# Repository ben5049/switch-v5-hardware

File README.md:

# Switch v5 Hardware (WIP)

KiCad design files for the 5th iteration of my single pair Ethernet (SPE) switch. It is similar to [v4](https://github.com/ben5049/switch-v4-hardware) but with more ports and an RJ45 connector so an external media converter isn't needed to connect to regular Ethernet networks.

## Versions

| Version | Description |
| ------- | ----------- |
| v5.1.0  | Fixed bugs from first revision |
| v5.0.0  | First release |

See the [errata](docs/errata.md) for details on bugs.

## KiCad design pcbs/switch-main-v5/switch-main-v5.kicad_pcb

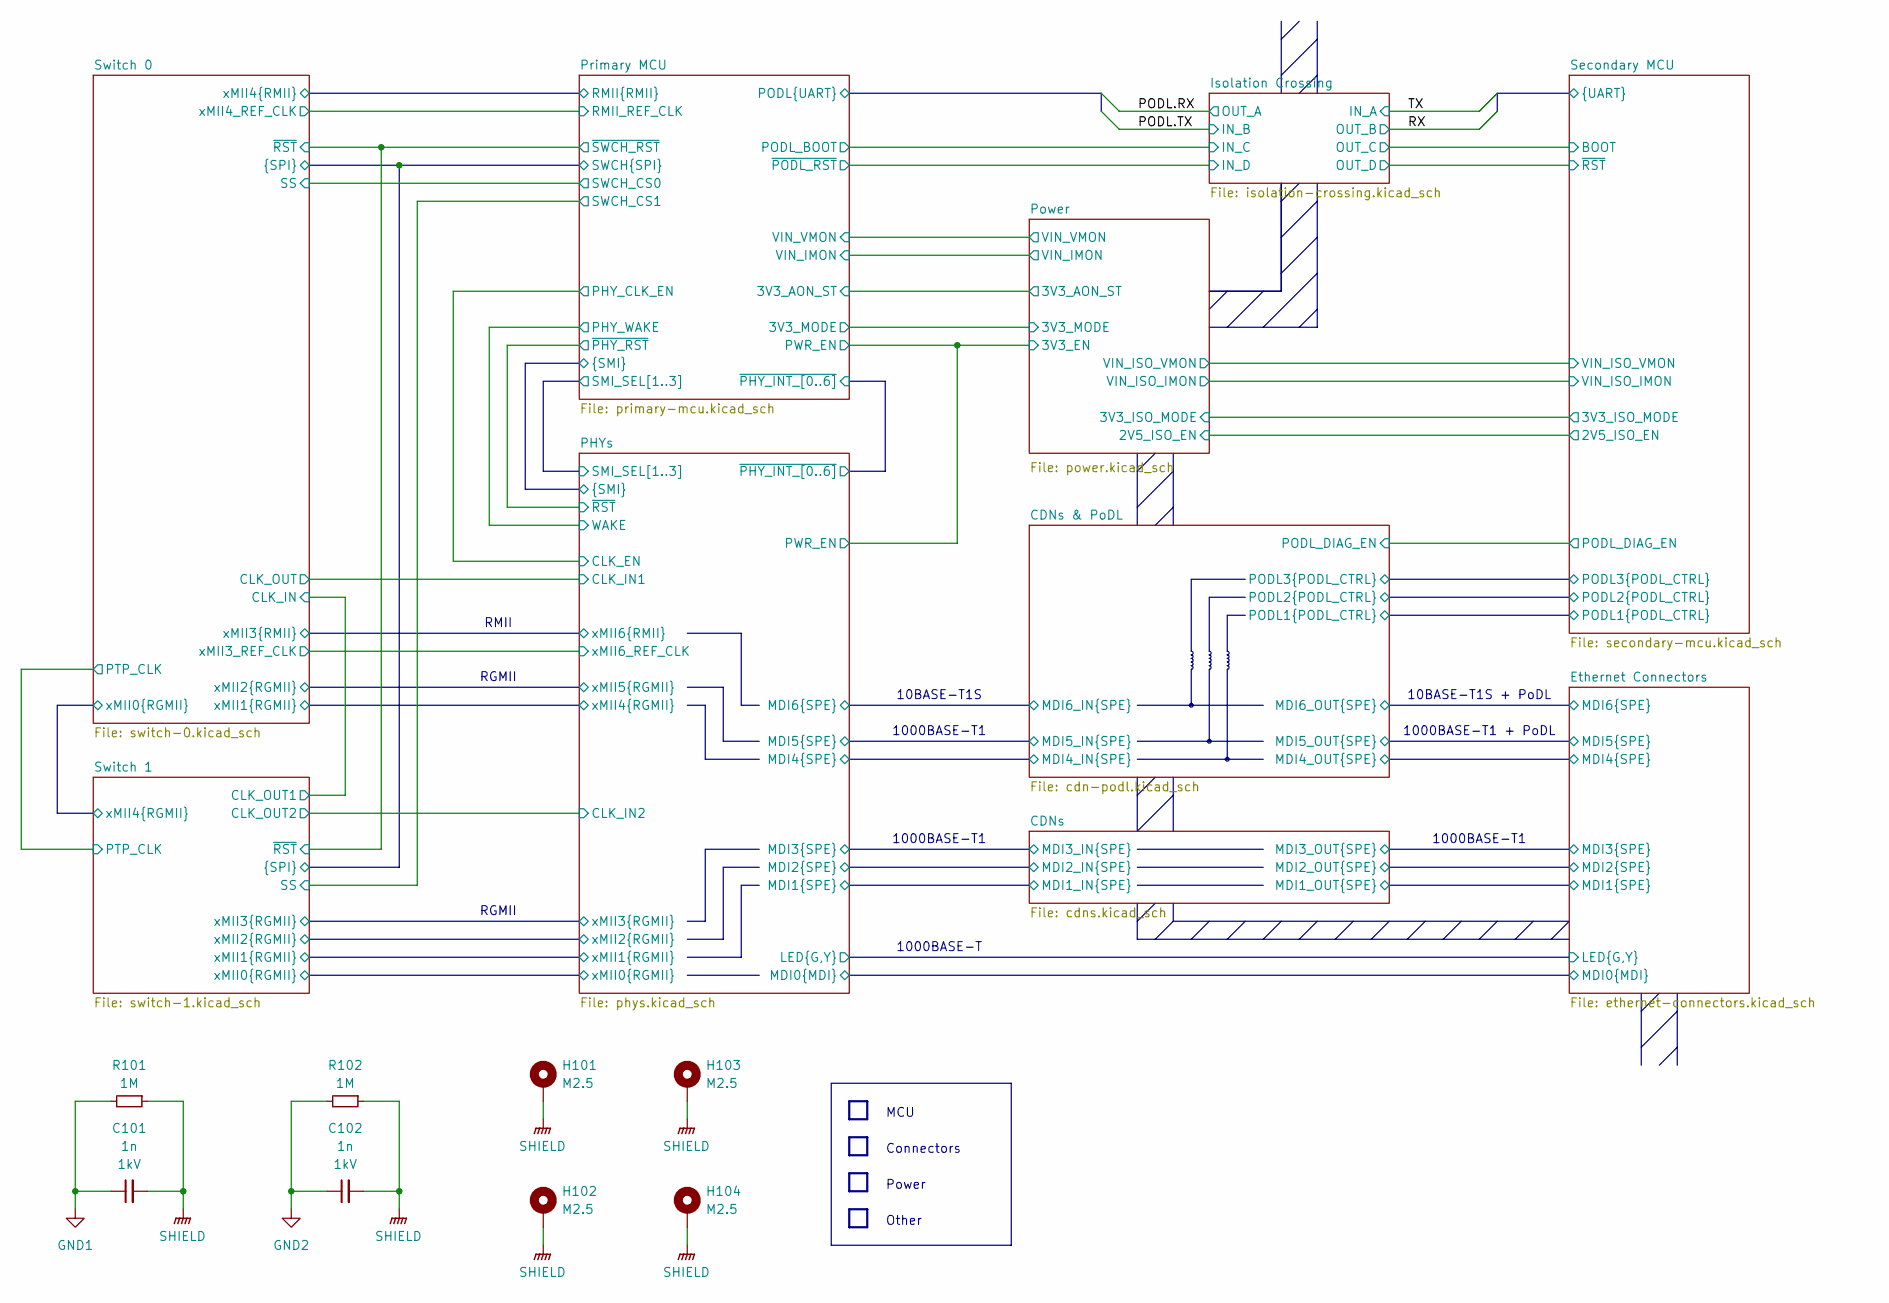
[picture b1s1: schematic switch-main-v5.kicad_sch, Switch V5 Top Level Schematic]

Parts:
C101, C102: 1n; C_0805; Voltage 1kV
H101, H102, H103, H104: M2.5; MountingHole_2.7mm_M2.5_Pad
R101, R102: 1M; R_0805

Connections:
GND1: C101.1, R101.2; also elsewhere on the board
GND2: C102.1, R102.2; also elsewhere on the board
SHIELD: C101.2, C102.2, H101.1 (1_1), H102.1 (1_1), H103.1 (1_1), H104.1 (1_1), R101.1, R102.1; also elsewhere on the board

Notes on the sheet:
10BASE-T1S
1000BASE-T1
Power
RGMII
Other
1000BASE-T
RMII
Connectors
1000BASE-T1 + PoDL
MCU
10BASE-T1S + PoDL

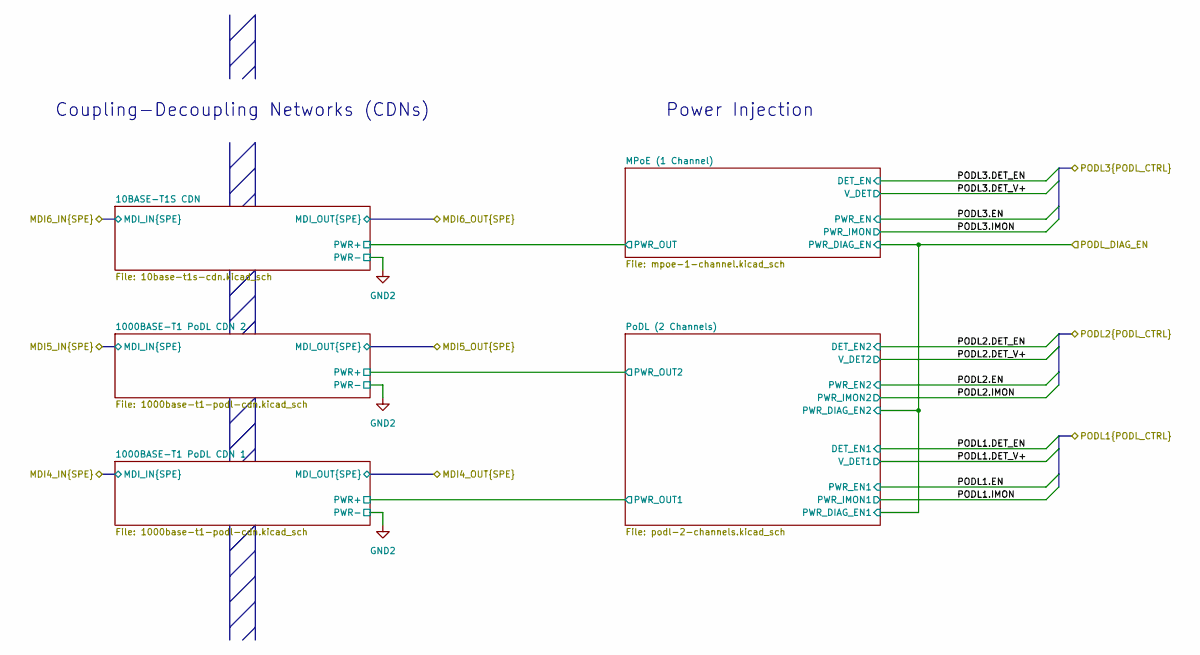
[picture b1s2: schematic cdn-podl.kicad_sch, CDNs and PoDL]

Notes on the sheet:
Power Injection
Coupling-Decoupling Networks (CDNs)

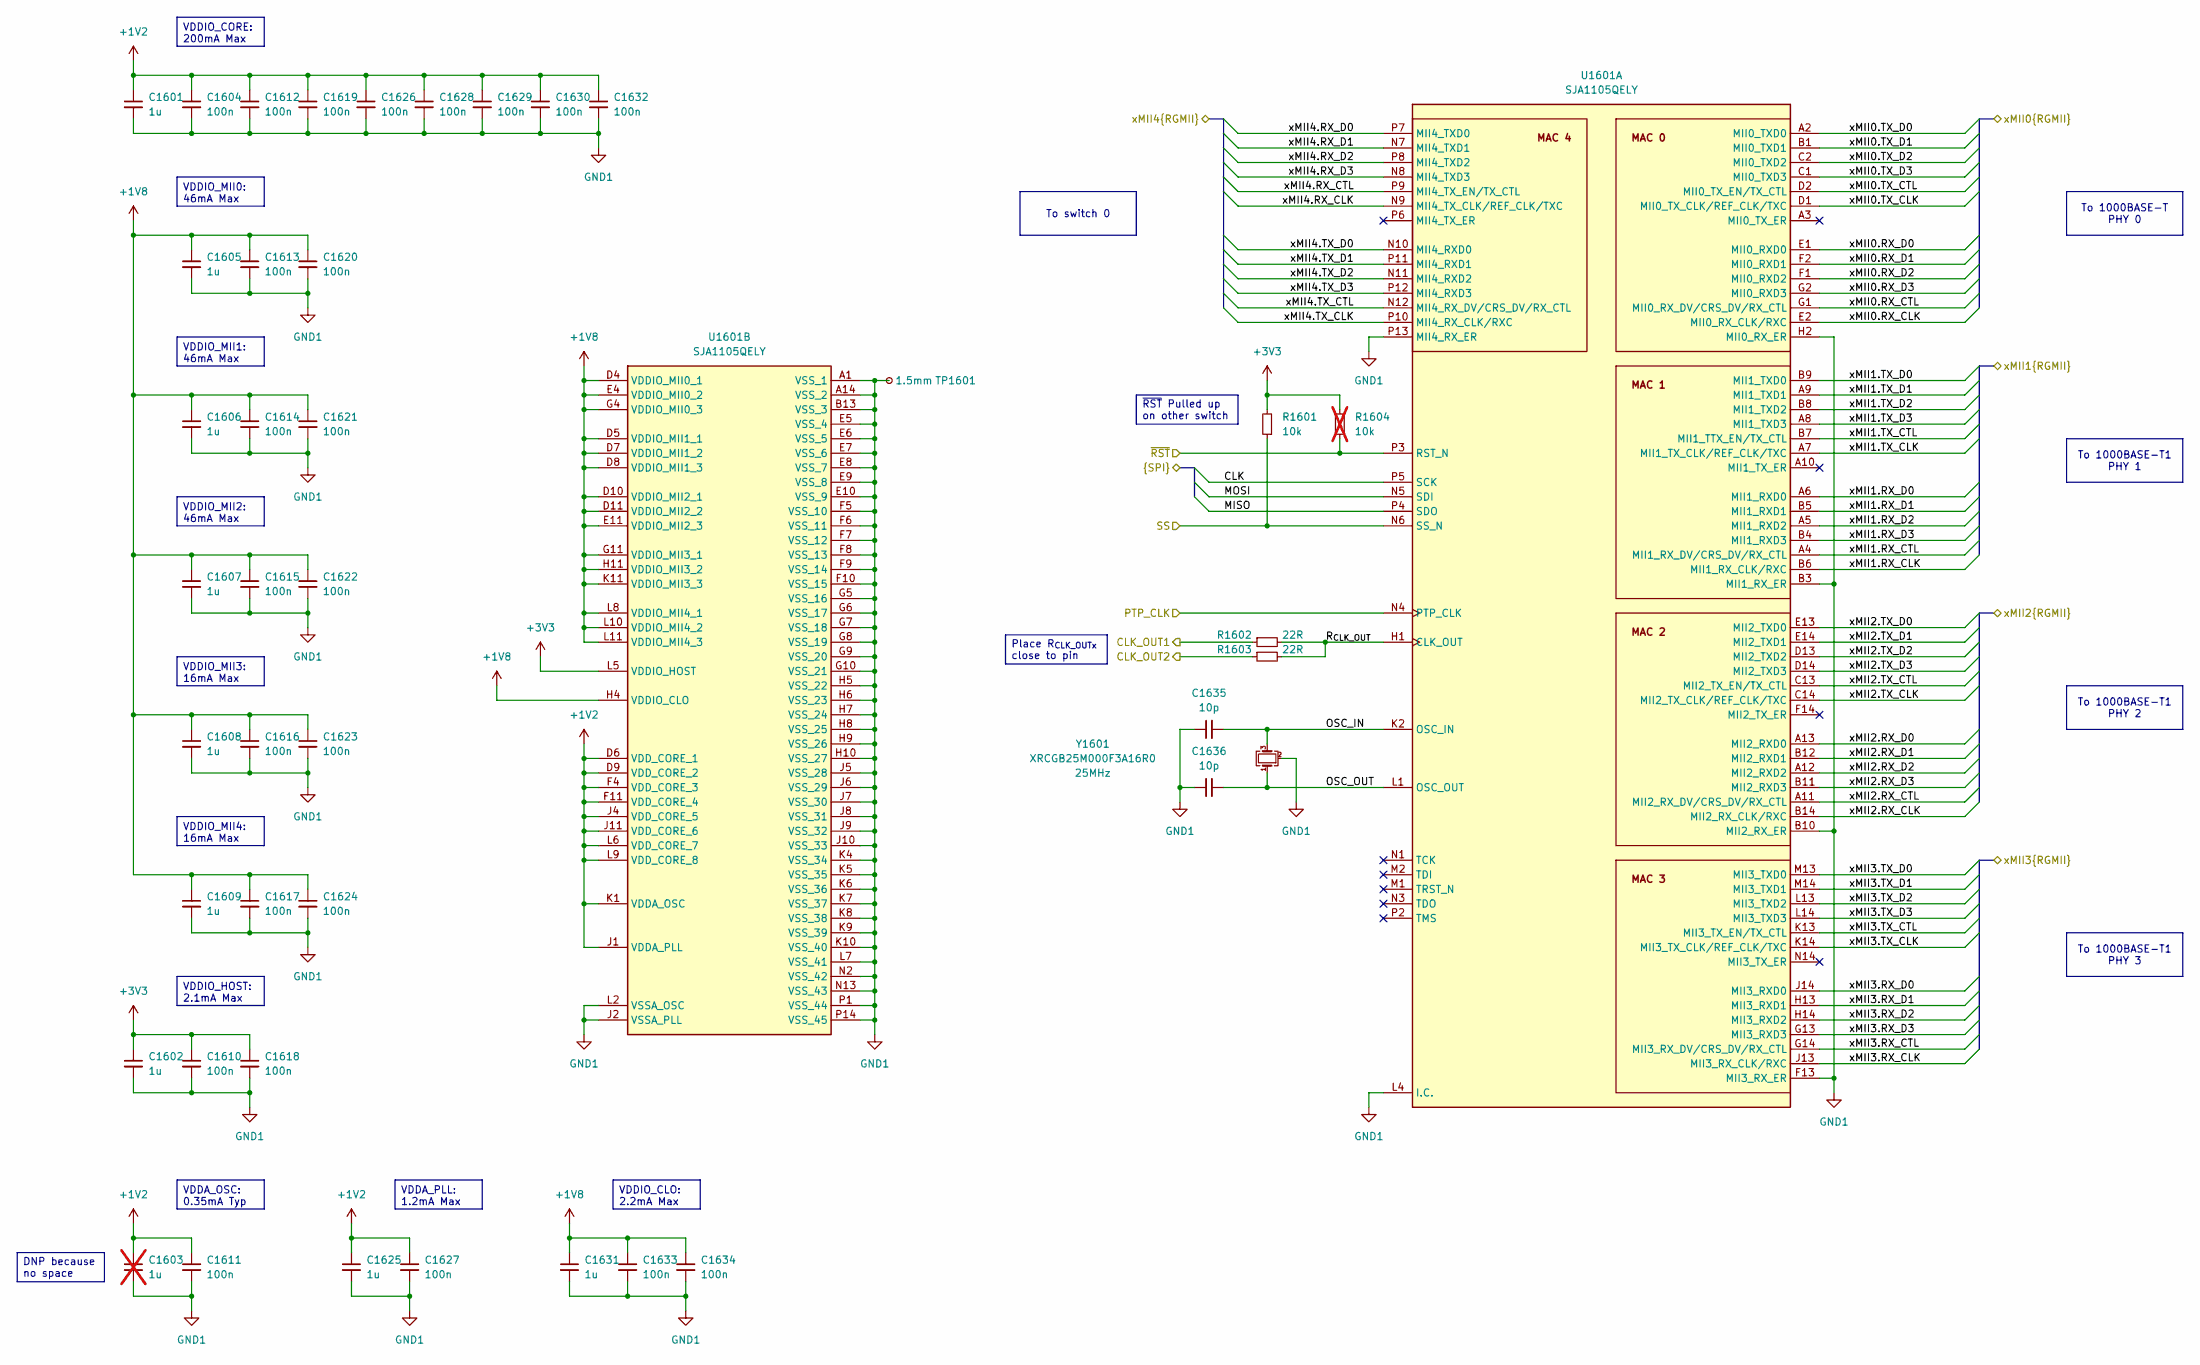
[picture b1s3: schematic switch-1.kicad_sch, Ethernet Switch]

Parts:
C1601, C1602, C1605, C1606, C1607, C1608, C1609, C1625, C1631: 1u; C_0402
C1603: 1u; C_0402_1005Metric; not fitted
C1604, C1610, C1611, C1612, C1613, C1614, C1615, C1616, C1617, C1618, C1619, C1620, C1621, C1622, C1623, C1624, C1626, C1627, C1628, C1629, C1630, C1632, C1633, C1634: 100n; C_0402
C1635, C1636: 10p; C_0402
R1601: 10k; R_0402
R1602, R1603: 22R; R_0402
R1604: 10k; R_0402_1005Metric; not fitted
TP1601: 1.5mm; TestPoint_Pad_D1.5mm
U1601: SJA1105QELY; BGA159C80P14X14_1200X1200X150; Mouser Part Number 771-SJA1105QELY
Y1601: XRCGB25M000F3A16R0

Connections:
+1V2: C1601.1, C1603.1, C1604.1, C1611.1, C1612.1, C1619.1, C1625.1, C1626.1, C1627.1, C1628.1, C1629.1, C1630.1, C1632.1, U1601.D6 (VDD_CORE_1), U1601.D9 (VDD_CORE_2), U1601.F4 (VDD_CORE_3), U1601.F11 (VDD_CORE_4), U1601.J1 (VDDA_PLL), U1601.J4 (VDD_CORE_5), U1601.J11 (VDD_CORE_6), U1601.K1 (VDDA_OSC), U1601.L6 (VDD_CORE_7), U1601.L9 (VDD_CORE_8); also elsewhere on the board
+1V8: C1605.1, C1606.1, C1607.1, C1608.1, C1609.1, C1613.1, C1614.1, C1615.1, C1616.1, C1617.1, C1620.1, C1621.1, C1622.1, C1623.1, C1624.1, C1631.1, C1633.1, C1634.1, U1601.D4 (VDDIO_MII0_1), U1601.D5 (VDDIO_MII1_1), U1601.D7 (VDDIO_MII1_2), U1601.D8 (VDDIO_MII1_3), U1601.D10 (VDDIO_MII2_1), U1601.D11 (VDDIO_MII2_2), U1601.E4 (VDDIO_MII0_2), U1601.E11 (VDDIO_MII2_3), U1601.G4 (VDDIO_MII0_3), U1601.G11 (VDDIO_MII3_1), U1601.H4 (VDDIO_CLO), U1601.H11 (VDDIO_MII3_2), U1601.K11 (VDDIO_MII3_3), U1601.L8 (VDDIO_MII4_1), U1601.L10 (VDDIO_MII4_2), U1601.L11 (VDDIO_MII4_3); also elsewhere on the board
+3V3: C1602.1, C1610.1, C1618.1, R1601.2, R1604.2, U1601.L5 (VDDIO_HOST); also elsewhere on the board
/PHYs/CLK_IN2: R1603.1; also elsewhere on the board
/PHYs/xMII0.RX_CLK: U1601.E2 (MII0_RX_CLK/RXC); also elsewhere on the board
/PHYs/xMII0.RX_CTL: U1601.G1 (MII0_RX_DV/CRS_DV/RX_CTL); also elsewhere on the board
/PHYs/xMII0.RX_D0: U1601.E1 (MII0_RXD0); also elsewhere on the board
/PHYs/xMII0.RX_D1: U1601.F2 (MII0_RXD1); also elsewhere on the board
/PHYs/xMII0.RX_D2: U1601.F1 (MII0_RXD2); also elsewhere on the board
/PHYs/xMII0.RX_D3: U1601.G2 (MII0_RXD3); also elsewhere on the board
/PHYs/xMII0.TX_CLK: U1601.D1 (MII0_TX_CLK/REF_CLK/TXC); also elsewhere on the board
/PHYs/xMII0.TX_CTL: U1601.D2 (MII0_TX_EN/TX_CTL); also elsewhere on the board
/PHYs/xMII0.TX_D0: U1601.A2 (MII0_TXD0); also elsewhere on the board
/PHYs/xMII0.TX_D1: U1601.B1 (MII0_TXD1); also elsewhere on the board
/PHYs/xMII0.TX_D2: U1601.C2 (MII0_TXD2); also elsewhere on the board
/PHYs/xMII0.TX_D3: U1601.C1 (MII0_TXD3); also elsewhere on the board
/PHYs/xMII1.RX_CLK: U1601.B6 (MII1_RX_CLK/RXC); also elsewhere on the board
/PHYs/xMII1.RX_CTL: U1601.A4 (MII1_RX_DV/CRS_DV/RX_CTL); also elsewhere on the board
/PHYs/xMII1.RX_D0: U1601.A6 (MII1_RXD0); also elsewhere on the board
/PHYs/xMII1.RX_D1: U1601.B5 (MII1_RXD1); also elsewhere on the board
/PHYs/xMII1.RX_D2: U1601.A5 (MII1_RXD2); also elsewhere on the board
/PHYs/xMII1.RX_D3: U1601.B4 (MII1_RXD3); also elsewhere on the board
/PHYs/xMII1.TX_CLK: U1601.A7 (MII1_TX_CLK/REF_CLK/TXC); also elsewhere on the board
/PHYs/xMII1.TX_CTL: U1601.B7 (MII1_TTX_EN/TX_CTL); also elsewhere on the board
/PHYs/xMII1.TX_D0: U1601.B9 (MII1_TXD0); also elsewhere on the board
/PHYs/xMII1.TX_D1: U1601.A9 (MII1_TXD1); also elsewhere on the board
/PHYs/xMII1.TX_D2: U1601.B8 (MII1_TXD2); also elsewhere on the board
/PHYs/xMII1.TX_D3: U1601.A8 (MII1_TXD3); also elsewhere on the board
/PHYs/xMII2.RX_CLK: U1601.B14 (MII2_RX_CLK/RXC); also elsewhere on the board
/PHYs/xMII2.RX_CTL: U1601.A11 (MII2_RX_DV/CRS_DV/RX_CTL); also elsewhere on the board
/PHYs/xMII2.RX_D0: U1601.A13 (MII2_RXD0); also elsewhere on the board
/PHYs/xMII2.RX_D1: U1601.B12 (MII2_RXD1); also elsewhere on the board
/PHYs/xMII2.RX_D2: U1601.A12 (MII2_RXD2); also elsewhere on the board
/PHYs/xMII2.RX_D3: U1601.B11 (MII2_RXD3); also elsewhere on the board
/PHYs/xMII2.TX_CLK: U1601.C14 (MII2_TX_CLK/REF_CLK/TXC); also elsewhere on the board
/PHYs/xMII2.TX_CTL: U1601.C13 (MII2_TX_EN/TX_CTL); also elsewhere on the board
/PHYs/xMII2.TX_D0: U1601.E13 (MII2_TXD0); also elsewhere on the board
/PHYs/xMII2.TX_D1: U1601.E14 (MII2_TXD1); also elsewhere on the board
/PHYs/xMII2.TX_D2: U1601.D13 (MII2_TXD2); also elsewhere on the board
/PHYs/xMII2.TX_D3: U1601.D14 (MII2_TXD3); also elsewhere on the board
/PHYs/xMII3.RX_CLK: U1601.J13 (MII3_RX_CLK/RXC); also elsewhere on the board
/PHYs/xMII3.RX_CTL: U1601.G14 (MII3_RX_DV/CRS_DV/RX_CTL); also elsewhere on the board
/PHYs/xMII3.RX_D0: U1601.J14 (MII3_RXD0); also elsewhere on the board
/PHYs/xMII3.RX_D1: U1601.H13 (MII3_RXD1); also elsewhere on the board
/PHYs/xMII3.RX_D2: U1601.H14 (MII3_RXD2); also elsewhere on the board
/PHYs/xMII3.RX_D3: U1601.G13 (MII3_RXD3); also elsewhere on the board
/PHYs/xMII3.TX_CLK: U1601.K14 (MII3_TX_CLK/REF_CLK/TXC); also elsewhere on the board
/PHYs/xMII3.TX_CTL: U1601.K13 (MII3_TX_EN/TX_CTL); also elsewhere on the board
/PHYs/xMII3.TX_D0: U1601.M13 (MII3_TXD0); also elsewhere on the board
/PHYs/xMII3.TX_D1: U1601.M14 (MII3_TXD1); also elsewhere on the board
/PHYs/xMII3.TX_D2: U1601.L13 (MII3_TXD2); also elsewhere on the board
/PHYs/xMII3.TX_D3: U1601.L14 (MII3_TXD3); also elsewhere on the board
/Primary MCU/SWCH.CLK: U1601.P5 (SCK); also elsewhere on the board
/Primary MCU/SWCH.MISO: U1601.P4 (SDO); also elsewhere on the board
/Primary MCU/SWCH.MOSI: U1601.N5 (SDI); also elsewhere on the board
/Primary MCU/SWCH_CS1: R1601.1, U1601.N6 (SS_N); also elsewhere on the board
/Primary MCU/~SWCH_RST: R1604.1, U1601.P3 (RST_N); also elsewhere on the board
/Switch 0/CLK_IN: R1602.1; also elsewhere on the board
/Switch 0/PTP_CLK: U1601.N4 (PTP_CLK); also elsewhere on the board
/Switch 0/xMII0.RX_CLK: U1601.N9 (MII4_TX_CLK/REF_CLK/TXC); also elsewhere on the board
/Switch 0/xMII0.RX_CTL: U1601.P9 (MII4_TX_EN/TX_CTL); also elsewhere on the board
/Switch 0/xMII0.RX_D0: U1601.P7 (MII4_TXD0); also elsewhere on the board
/Switch 0/xMII0.RX_D1: U1601.N7 (MII4_TXD1); also elsewhere on the board
/Switch 0/xMII0.RX_D2: U1601.P8 (MII4_TXD2); also elsewhere on the board
/Switch 0/xMII0.RX_D3: U1601.N8 (MII4_TXD3); also elsewhere on the board
/Switch 0/xMII0.TX_CLK: U1601.P10 (MII4_RX_CLK/RXC); also elsewhere on the board
/Switch 0/xMII0.TX_CTL: U1601.N12 (MII4_RX_DV/CRS_DV/RX_CTL); also elsewhere on the board
/Switch 0/xMII0.TX_D0: U1601.N10 (MII4_RXD0); also elsewhere on the board
/Switch 0/xMII0.TX_D1: U1601.P11 (MII4_RXD1); also elsewhere on the board
/Switch 0/xMII0.TX_D2: U1601.N11 (MII4_RXD2); also elsewhere on the board
/Switch 0/xMII0.TX_D3: U1601.P12 (MII4_RXD3); also elsewhere on the board
/Switch 1/OSC_IN: C1635.2, U1601.K2 (OSC_IN), Y1601.3
/Switch 1/OSC_OUT: C1636.2, U1601.L1 (OSC_OUT), Y1601.1
/Switch 1/R_{CLK_OUT}: R1602.2, R1603.2, U1601.H1 (CLK_OUT)
GND1: C1601.2, C1602.2, C1603.2, C1604.2, C1605.2, C1606.2, C1607.2, C1608.2, C1609.2, C1610.2, C1611.2, C1612.2, C1613.2, C1614.2, C1615.2, C1616.2, C1617.2, C1618.2, C1619.2, C1620.2, C1621.2, C1622.2, C1623.2, C1624.2, C1625.2, C1626.2, C1627.2, C1628.2, C1629.2, C1630.2, C1631.2, C1632.2, C1633.2, C1634.2, C1635.1, C1636.1, TP1601.1 (1_1), U1601.A1 (VSS_1), U1601.A14 (VSS_2), U1601.B3 (MII1_RX_ER), U1601.B10 (MII2_RX_ER), U1601.B13 (VSS_3), U1601.E5 (VSS_4), U1601.E6 (VSS_5), U1601.E7 (VSS_6), U1601.E8 (VSS_7), U1601.E9 (VSS_8), U1601.E10 (VSS_9), U1601.F5 (VSS_10), U1601.F6 (VSS_11), U1601.F7 (VSS_12), U1601.F8 (VSS_13), U1601.F9 (VSS_14), U1601.F10 (VSS_15), U1601.F13 (MII3_RX_ER), U1601.G5 (VSS_16), U1601.G6 (VSS_17), U1601.G7 (VSS_18), U1601.G8 (VSS_19), U1601.G9 (VSS_20), U1601.G10 (VSS_21), U1601.H2 (MII0_RX_ER), U1601.H5 (VSS_22), U1601.H6 (VSS_23), U1601.H7 (VSS_24), U1601.H8 (VSS_25), U1601.H9 (VSS_26), U1601.H10 (VSS_27), U1601.J2 (VSSA_PLL), U1601.J5 (VSS_28), U1601.J6 (VSS_29), U1601.J7 (VSS_30), U1601.J8 (VSS_31), U1601.J9 (VSS_32), U1601.J10 (VSS_33), U1601.K4 (VSS_34), U1601.K5 (VSS_35), U1601.K6 (VSS_36), U1601.K7 (VSS_37), U1601.K8 (VSS_38), U1601.K9 (VSS_39), U1601.K10 (VSS_40), U1601.L2 (VSSA_OSC), U1601.L4 (I.C.), U1601.L7 (VSS_41), U1601.N2 (VSS_42), U1601.N13 (VSS_43), U1601.P1 (VSS_44), U1601.P13 (MII4_RX_ER), U1601.P14 (VSS_45), Y1601.2 (G), Y1601.4 (G); also elsewhere on the board

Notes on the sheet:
To 1000BASE-T1 PHY 1
To 1000BASE-T1 PHY 2
VDDIO_MII3: 16mA Max
~{RST} Pulled up on other switch
To 1000BASE-T1 PHY 3
VDDIO_CLO: 2.2mA Max
VDDIO_MII2: 46mA Max
VDDIO_HOST: 2.1mA Max
VDDA_OSC: 0.35mA Typ
DNP because no space
VDDIO_MII0: 46mA Max
To switch 0
VDDA_PLL: 1.2mA Max
VDDIO_CORE: 200mA Max
Place R_{CLK_OUTx} close to pin
To 1000BASE-T PHY 0
VDDIO_MII4: 16mA Max
VDDIO_MII1: 46mA Max

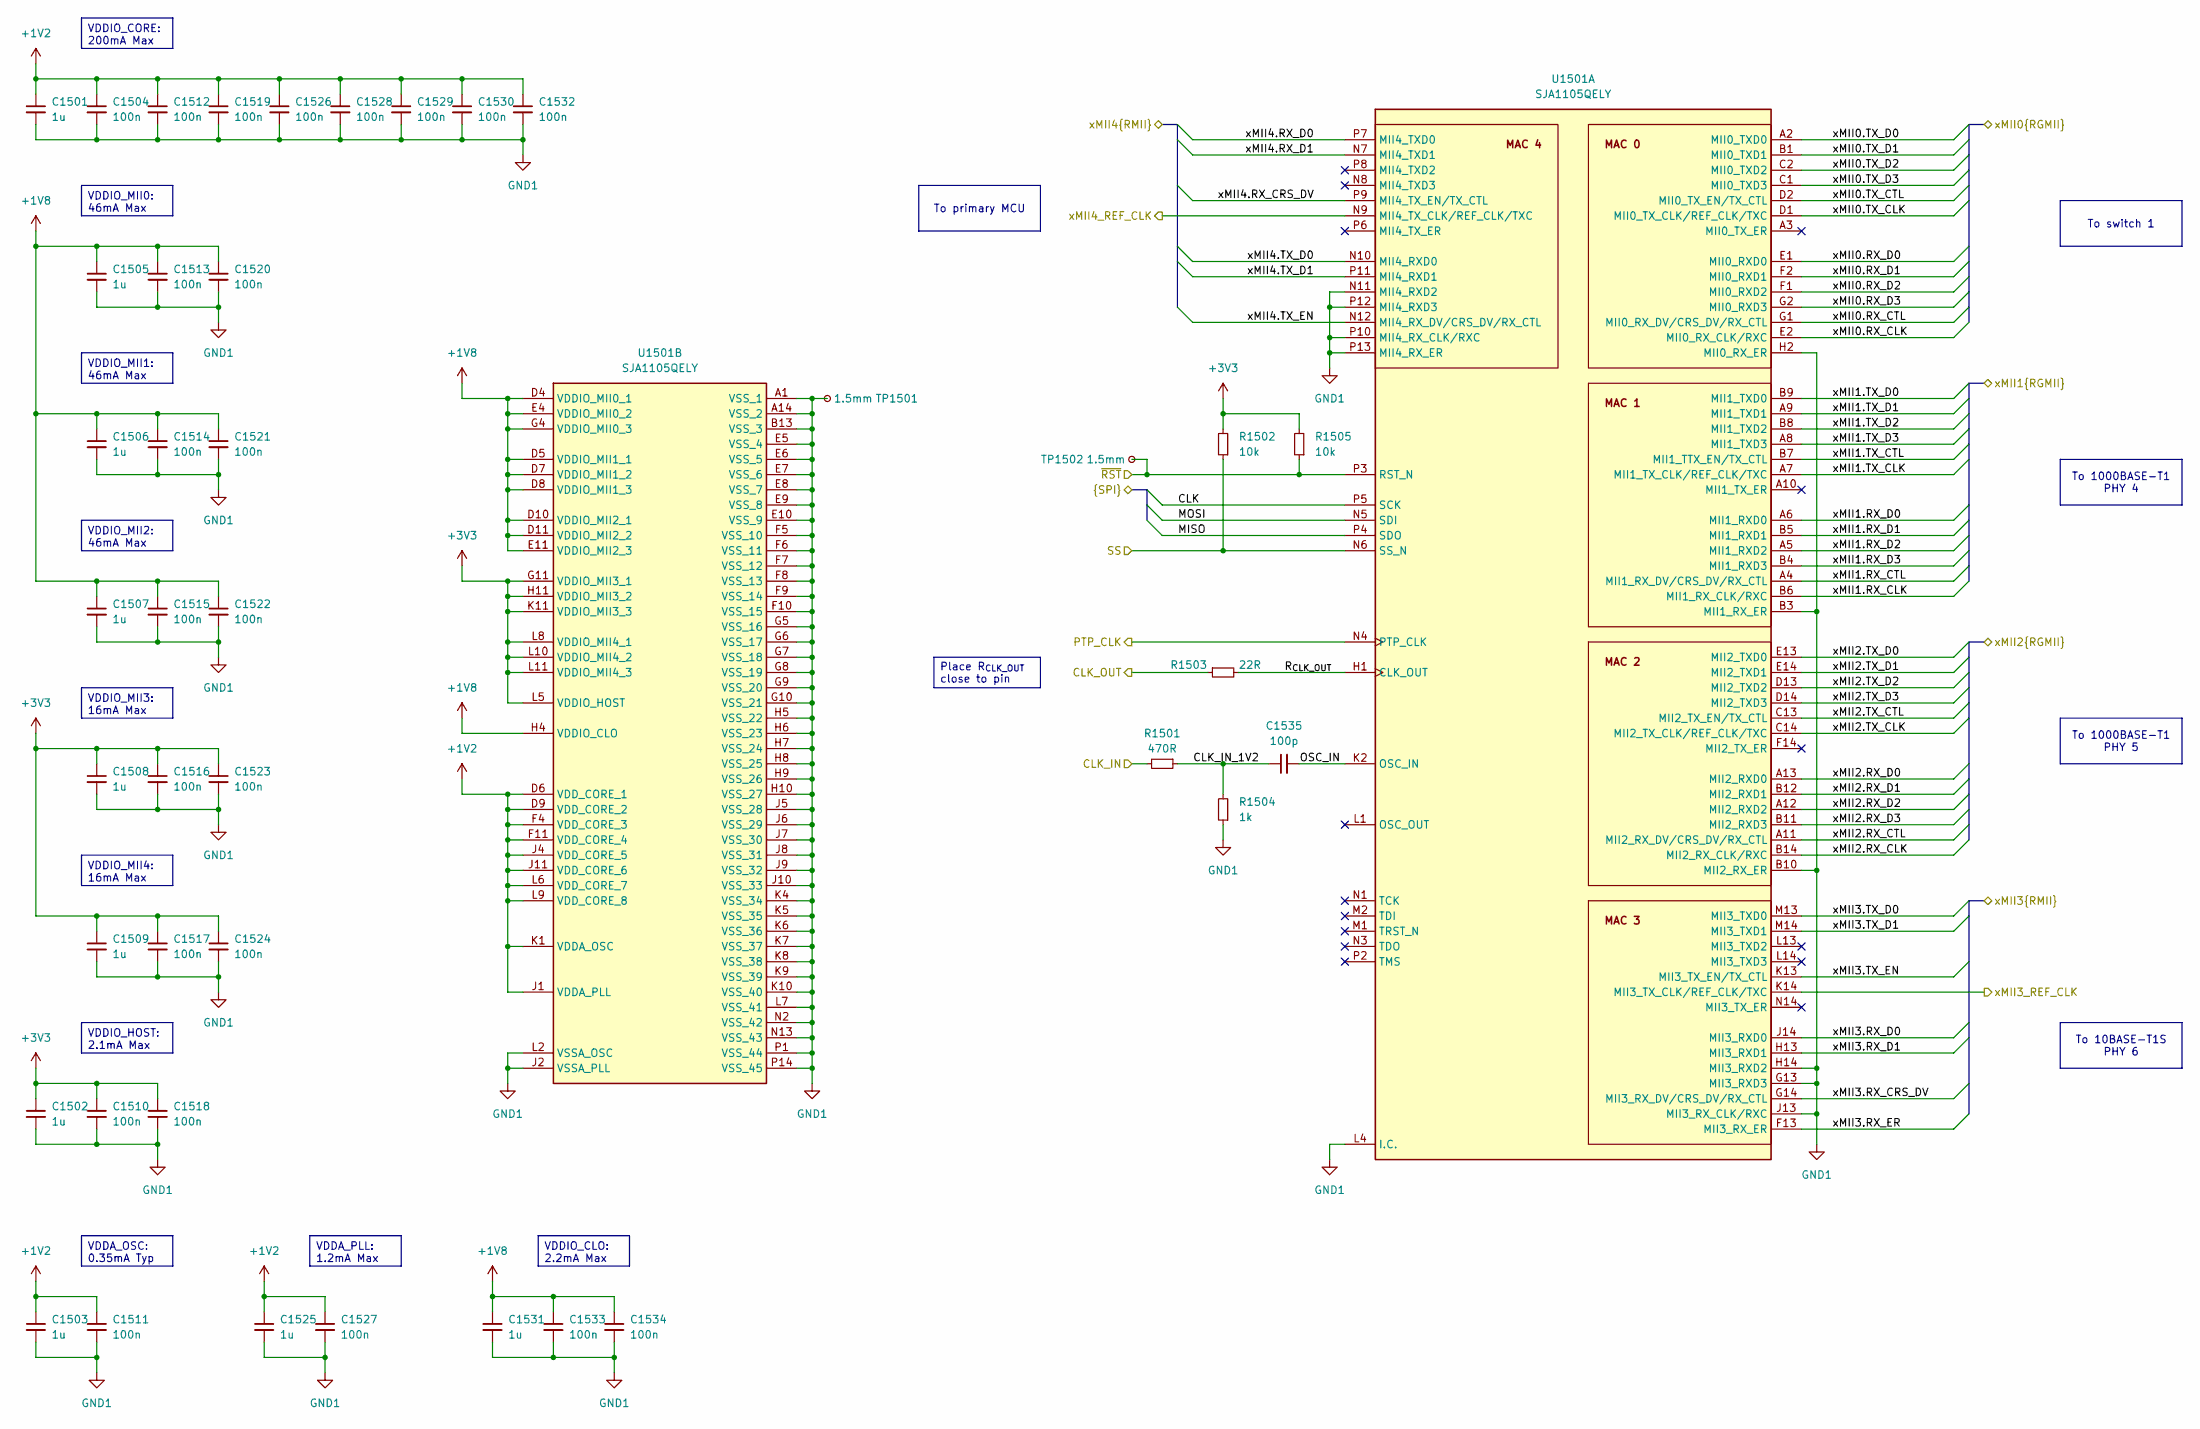
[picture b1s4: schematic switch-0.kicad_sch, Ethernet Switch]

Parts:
C1501, C1502, C1503, C1505, C1506, C1507, C1508, C1509, C1525, C1531: 1u; C_0402
C1504, C1510, C1511, C1512, C1513, C1514, C1515, C1516, C1517, C1518, C1519, C1520, C1521, C1522, C1523, C1524, C1526, C1527, C1528, C1529, C1530, C1532, C1533, C1534: 100n; C_0402
C1535: 100p; C_0402
R1501: 470R; R_0402
R1502, R1505: 10k; R_0402
R1503: 22R; R_0402
R1504: 1k; R_0402
TP1501, TP1502: 1.5mm; TestPoint_Pad_D1.5mm
U1501: SJA1105QELY; BGA159C80P14X14_1200X1200X150; Mouser Part Number 771-SJA1105QELY

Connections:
+1V2: C1501.1, C1503.1, C1504.1, C1511.1, C1512.1, C1519.1, C1525.1, C1526.1, C1527.1, C1528.1, C1529.1, C1530.1, C1532.1, U1501.D6 (VDD_CORE_1), U1501.D9 (VDD_CORE_2), U1501.F4 (VDD_CORE_3), U1501.F11 (VDD_CORE_4), U1501.J1 (VDDA_PLL), U1501.J4 (VDD_CORE_5), U1501.J11 (VDD_CORE_6), U1501.K1 (VDDA_OSC), U1501.L6 (VDD_CORE_7), U1501.L9 (VDD_CORE_8); also elsewhere on the board
+1V8: C1505.1, C1506.1, C1507.1, C1513.1, C1514.1, C1515.1, C1520.1, C1521.1, C1522.1, C1531.1, C1533.1, C1534.1, U1501.D4 (VDDIO_MII0_1), U1501.D5 (VDDIO_MII1_1), U1501.D7 (VDDIO_MII1_2), U1501.D8 (VDDIO_MII1_3), U1501.D10 (VDDIO_MII2_1), U1501.D11 (VDDIO_MII2_2), U1501.E4 (VDDIO_MII0_2), U1501.E11 (VDDIO_MII2_3), U1501.G4 (VDDIO_MII0_3), U1501.H4 (VDDIO_CLO); also elsewhere on the board
+3V3: C1502.1, C1508.1, C1509.1, C1510.1, C1516.1, C1517.1, C1518.1, C1523.1, C1524.1, R1502.2, R1505.2, U1501.G11 (VDDIO_MII3_1), U1501.H11 (VDDIO_MII3_2), U1501.K11 (VDDIO_MII3_3), U1501.L5 (VDDIO_HOST), U1501.L8 (VDDIO_MII4_1), U1501.L10 (VDDIO_MII4_2), U1501.L11 (VDDIO_MII4_3); also elsewhere on the board
/PHYs/CLK_IN1: R1503.1; also elsewhere on the board
/PHYs/xMII4.RX_CLK: U1501.B6 (MII1_RX_CLK/RXC); also elsewhere on the board
/PHYs/xMII4.RX_CTL: U1501.A4 (MII1_RX_DV/CRS_DV/RX_CTL); also elsewhere on the board
/PHYs/xMII4.RX_D0: U1501.A6 (MII1_RXD0); also elsewhere on the board
/PHYs/xMII4.RX_D1: U1501.B5 (MII1_RXD1); also elsewhere on the board
/PHYs/xMII4.RX_D2: U1501.A5 (MII1_RXD2); also elsewhere on the board
/PHYs/xMII4.RX_D3: U1501.B4 (MII1_RXD3); also elsewhere on the board
/PHYs/xMII4.TX_CLK: U1501.A7 (MII1_TX_CLK/REF_CLK/TXC); also elsewhere on the board
/PHYs/xMII4.TX_CTL: U1501.B7 (MII1_TTX_EN/TX_CTL); also elsewhere on the board
/PHYs/xMII4.TX_D0: U1501.B9 (MII1_TXD0); also elsewhere on the board
/PHYs/xMII4.TX_D1: U1501.A9 (MII1_TXD1); also elsewhere on the board
/PHYs/xMII4.TX_D2: U1501.B8 (MII1_TXD2); also elsewhere on the board
/PHYs/xMII4.TX_D3: U1501.A8 (MII1_TXD3); also elsewhere on the board
/PHYs/xMII5.RX_CLK: U1501.B14 (MII2_RX_CLK/RXC); also elsewhere on the board
/PHYs/xMII5.RX_CTL: U1501.A11 (MII2_RX_DV/CRS_DV/RX_CTL); also elsewhere on the board
/PHYs/xMII5.RX_D0: U1501.A13 (MII2_RXD0); also elsewhere on the board
/PHYs/xMII5.RX_D1: U1501.B12 (MII2_RXD1); also elsewhere on the board
/PHYs/xMII5.RX_D2: U1501.A12 (MII2_RXD2); also elsewhere on the board
/PHYs/xMII5.RX_D3: U1501.B11 (MII2_RXD3); also elsewhere on the board
/PHYs/xMII5.TX_CLK: U1501.C14 (MII2_TX_CLK/REF_CLK/TXC); also elsewhere on the board
/PHYs/xMII5.TX_CTL: U1501.C13 (MII2_TX_EN/TX_CTL); also elsewhere on the board
/PHYs/xMII5.TX_D0: U1501.E13 (MII2_TXD0); also elsewhere on the board
/PHYs/xMII5.TX_D1: U1501.E14 (MII2_TXD1); also elsewhere on the board
/PHYs/xMII5.TX_D2: U1501.D13 (MII2_TXD2); also elsewhere on the board
/PHYs/xMII5.TX_D3: U1501.D14 (MII2_TXD3); also elsewhere on the board
/PHYs/xMII6.RX_CRS_DV: U1501.G14 (MII3_RX_DV/CRS_DV/RX_CTL); also elsewhere on the board
/PHYs/xMII6.RX_D0: U1501.J14 (MII3_RXD0); also elsewhere on the board
/PHYs/xMII6.RX_D1: U1501.H13 (MII3_RXD1); also elsewhere on the board
/PHYs/xMII6.RX_ER: U1501.F13 (MII3_RX_ER); also elsewhere on the board
/PHYs/xMII6.TX_D0: U1501.M13 (MII3_TXD0); also elsewhere on the board
/PHYs/xMII6.TX_D1: U1501.M14 (MII3_TXD1); also elsewhere on the board
/PHYs/xMII6.TX_EN: U1501.K13 (MII3_TX_EN/TX_CTL); also elsewhere on the board
/PHYs/xMII6_REF_CLK: U1501.K14 (MII3_TX_CLK/REF_CLK/TXC); also elsewhere on the board
/Primary MCU/RMII.RX_CRS_DV: U1501.P9 (MII4_TX_EN/TX_CTL); also elsewhere on the board
/Primary MCU/RMII.RX_D0: U1501.P7 (MII4_TXD0); also elsewhere on the board
/Primary MCU/RMII.RX_D1: U1501.N7 (MII4_TXD1); also elsewhere on the board
/Primary MCU/RMII.TX_D0: U1501.N10 (MII4_RXD0); also elsewhere on the board
/Primary MCU/RMII.TX_D1: U1501.P11 (MII4_RXD1); also elsewhere on the board
/Primary MCU/RMII.TX_EN: U1501.N12 (MII4_RX_DV/CRS_DV/RX_CTL); also elsewhere on the board
/Primary MCU/RMII_REF_CLK: U1501.N9 (MII4_TX_CLK/REF_CLK/TXC); also elsewhere on the board
/Primary MCU/SWCH.CLK: U1501.P5 (SCK); also elsewhere on the board
/Primary MCU/SWCH.MISO: U1501.P4 (SDO); also elsewhere on the board
/Primary MCU/SWCH.MOSI: U1501.N5 (SDI); also elsewhere on the board
/Primary MCU/SWCH_CS0: R1502.1, U1501.N6 (SS_N); also elsewhere on the board
/Primary MCU/~SWCH_RST: R1505.1, TP1502.1 (1_1), U1501.P3 (RST_N); also elsewhere on the board
/Switch 0/CLK_IN: R1501.2; also elsewhere on the board
/Switch 0/CLK_IN_1V2: C1535.1, R1501.1, R1504.2
/Switch 0/OSC_IN: C1535.2, U1501.K2 (OSC_IN)
/Switch 0/PTP_CLK: U1501.N4 (PTP_CLK); also elsewhere on the board
/Switch 0/R_{CLK_OUT}: R1503.2, U1501.H1 (CLK_OUT)
/Switch 0/xMII0.RX_CLK: U1501.E2 (MII0_RX_CLK/RXC); also elsewhere on the board
/Switch 0/xMII0.RX_CTL: U1501.G1 (MII0_RX_DV/CRS_DV/RX_CTL); also elsewhere on the board
/Switch 0/xMII0.RX_D0: U1501.E1 (MII0_RXD0); also elsewhere on the board
/Switch 0/xMII0.RX_D1: U1501.F2 (MII0_RXD1); also elsewhere on the board
/Switch 0/xMII0.RX_D2: U1501.F1 (MII0_RXD2); also elsewhere on the board
/Switch 0/xMII0.RX_D3: U1501.G2 (MII0_RXD3); also elsewhere on the board
/Switch 0/xMII0.TX_CLK: U1501.D1 (MII0_TX_CLK/REF_CLK/TXC); also elsewhere on the board
/Switch 0/xMII0.TX_CTL: U1501.D2 (MII0_TX_EN/TX_CTL); also elsewhere on the board
/Switch 0/xMII0.TX_D0: U1501.A2 (MII0_TXD0); also elsewhere on the board
/Switch 0/xMII0.TX_D1: U1501.B1 (MII0_TXD1); also elsewhere on the board
/Switch 0/xMII0.TX_D2: U1501.C2 (MII0_TXD2); also elsewhere on the board
/Switch 0/xMII0.TX_D3: U1501.C1 (MII0_TXD3); also elsewhere on the board
GND1: C1501.2, C1502.2, C1503.2, C1504.2, C1505.2, C1506.2, C1507.2, C1508.2, C1509.2, C1510.2, C1511.2, C1512.2, C1513.2, C1514.2, C1515.2, C1516.2, C1517.2, C1518.2, C1519.2, C1520.2, C1521.2, C1522.2, C1523.2, C1524.2, C1525.2, C1526.2, C1527.2, C1528.2, C1529.2, C1530.2, C1531.2, C1532.2, C1533.2, C1534.2, R1504.1, TP1501.1 (1_1), U1501.A1 (VSS_1), U1501.A14 (VSS_2), U1501.B3 (MII1_RX_ER), U1501.B10 (MII2_RX_ER), U1501.B13 (VSS_3), U1501.E5 (VSS_4), U1501.E6 (VSS_5), U1501.E7 (VSS_6), U1501.E8 (VSS_7), U1501.E9 (VSS_8), U1501.E10 (VSS_9), U1501.F5 (VSS_10), U1501.F6 (VSS_11), U1501.F7 (VSS_12), U1501.F8 (VSS_13), U1501.F9 (VSS_14), U1501.F10 (VSS_15), U1501.G5 (VSS_16), U1501.G6 (VSS_17), U1501.G7 (VSS_18), U1501.G8 (VSS_19), U1501.G9 (VSS_20), U1501.G10 (VSS_21), U1501.G13 (MII3_RXD3), U1501.H2 (MII0_RX_ER), U1501.H5 (VSS_22), U1501.H6 (VSS_23), U1501.H7 (VSS_24), U1501.H8 (VSS_25), U1501.H9 (VSS_26), U1501.H10 (VSS_27), U1501.H14 (MII3_RXD2), U1501.J2 (VSSA_PLL), U1501.J5 (VSS_28), U1501.J6 (VSS_29), U1501.J7 (VSS_30), U1501.J8 (VSS_31), U1501.J9 (VSS_32), U1501.J10 (VSS_33), U1501.J13 (MII3_RX_CLK/RXC), U1501.K4 (VSS_34), U1501.K5 (VSS_35), U1501.K6 (VSS_36), U1501.K7 (VSS_37), U1501.K8 (VSS_38), U1501.K9 (VSS_39), U1501.K10 (VSS_40), U1501.L2 (VSSA_OSC), U1501.L4 (I.C.), U1501.L7 (VSS_41), U1501.N2 (VSS_42), U1501.N11 (MII4_RXD2), U1501.N13 (VSS_43), U1501.P1 (VSS_44), U1501.P10 (MII4_RX_CLK/RXC), U1501.P12 (MII4_RXD3), U1501.P13 (MII4_RX_ER), U1501.P14 (VSS_45); also elsewhere on the board

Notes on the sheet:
To 1000BASE-T1 PHY 4
To 1000BASE-T1 PHY 5
VDDIO_MII3: 16mA Max
VDDIO_CLO: 2.2mA Max
VDDIO_MII2: 46mA Max
VDDIO_HOST: 2.1mA Max
VDDA_OSC: 0.35mA Typ
VDDIO_MII0: 46mA Max
To 10BASE-T1S PHY 6
VDDA_PLL: 1.2mA Max
VDDIO_CORE: 200mA Max
Place R_{CLK_OUT} close to pin
To switch 1
VDDIO_MII4: 16mA Max
To primary MCU
VDDIO_MII1: 46mA Max

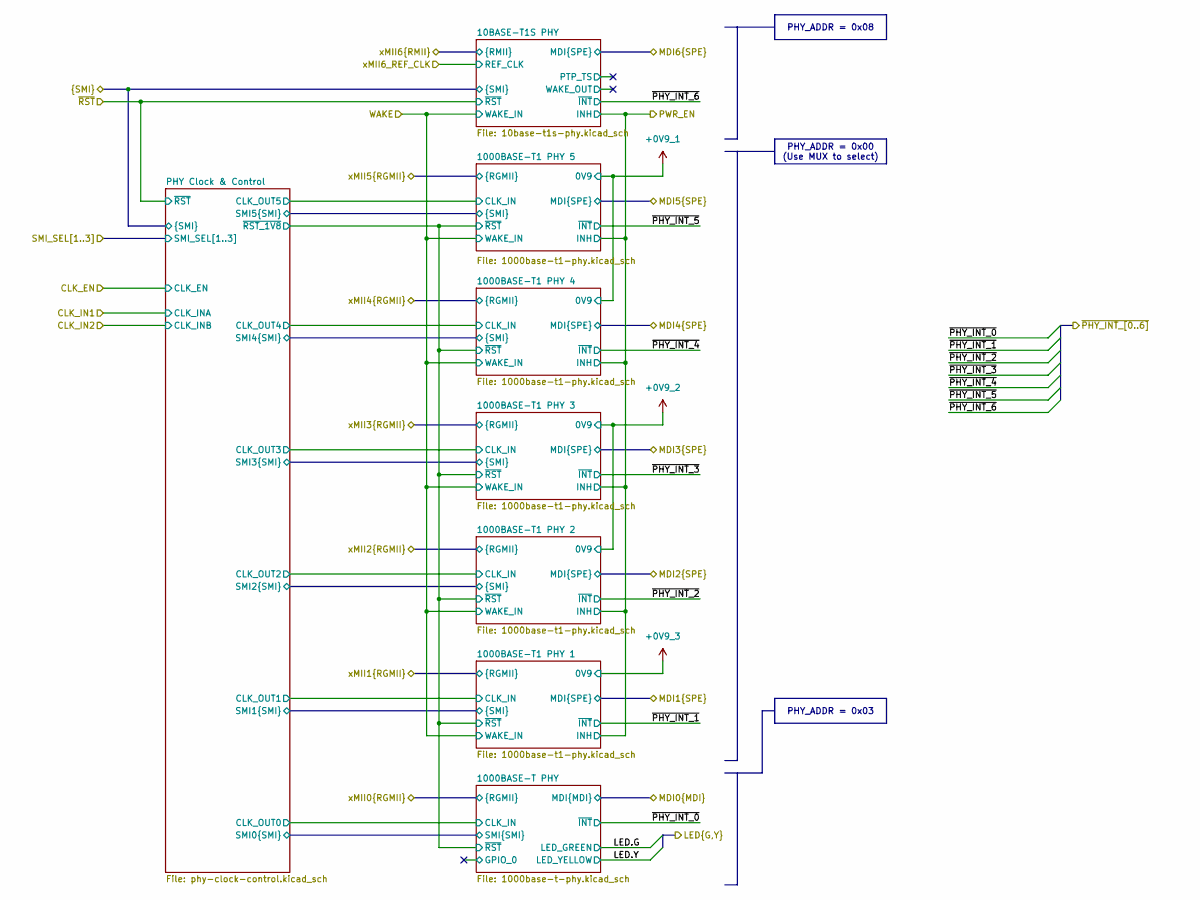
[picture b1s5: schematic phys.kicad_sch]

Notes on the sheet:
PHY_ADDR = 0x03
PHY_ADDR = 0x00 (Use MUX to select)
PHY_ADDR = 0x08

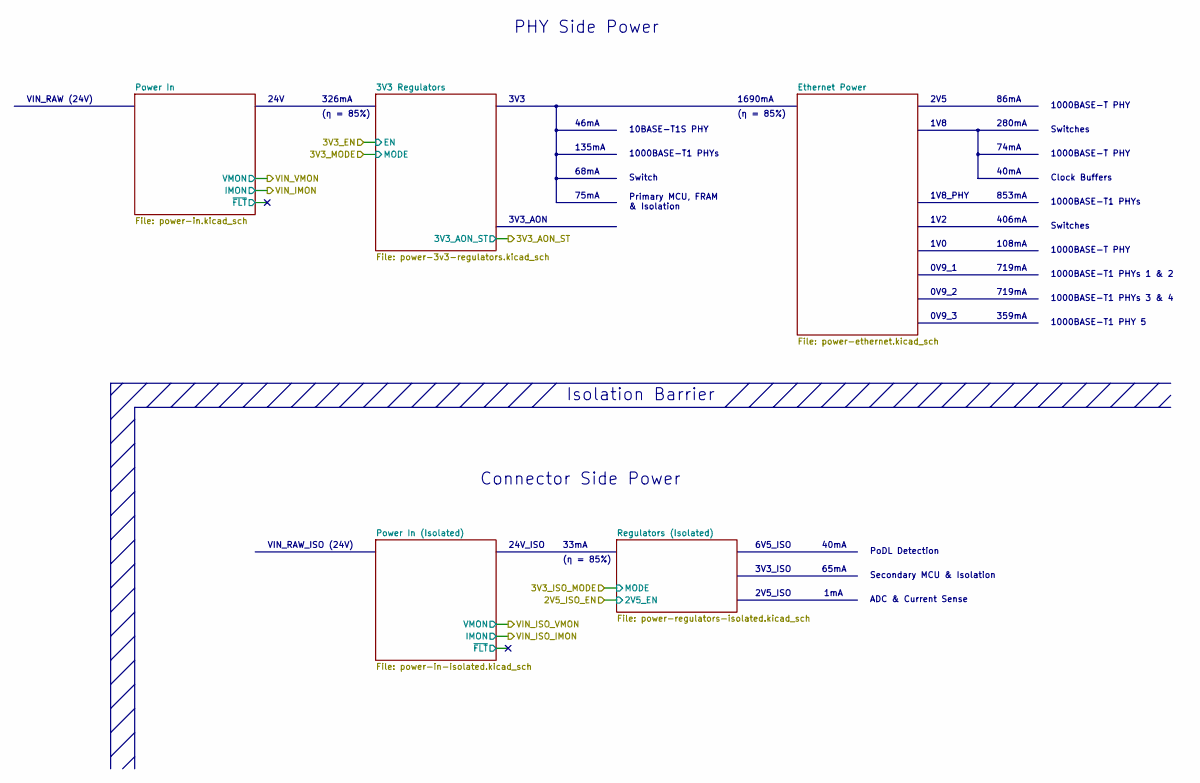
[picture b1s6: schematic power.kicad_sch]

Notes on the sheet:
1V2
Primary MCU, FRAM & Isolation
VIN_RAW_ISO (24V)
68mA
135mA
VIN_RAW (24V)
719mA
1V0
(η = 85%)
2V5
Clock Buffers
Switch
40mA
1V8
0V9_2
1000BASE-T PHY
10BASE-T1S PHY
3V3
853mA
280mA
24V_ISO
33mA
74mA
1mA
46mA
1000BASE-T1 PHYs
1000BASE-T1 PHYs 1 & 2
24V
Switches
1690mA
PHY Side Power
326mA
1V8_PHY
1000BASE-T1 PHY 5
6V5_ISO
359mA
Isolation Barrier
PoDL Detection
2V5_ISO
Connector Side Power
